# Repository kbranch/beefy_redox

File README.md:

# Beefy Redox
This uses the Redox layout with significant modifications to make it feel and sound sturdy.  It's dumb and overkill, but I like it.  PCB has been redone to work with Kailh MX hotswap sockets because Mill-Max sockets don't really fit some switches (like Kailh's box series).

Based on Mattia Dal Ben's Redox keyboard: https://github.com/mattdibi/redox-keyboard

Case based on Fosk_LL's design: https://www.thingiverse.com/thing:3607303

Associated hacked together firmware: https://github.com/kbranch/qmk_beefy_redox

Disasterous CAD files are available here:
https://cad.onshape.com/documents/79753b5942c6535c2d806763/w/4c8392e04a1d78f77636699a/e/d620deb7dfbc2bdc09fda4c7
https://cad.onshape.com/documents/7a9b7e869b26a13f2521e861/w/94ad519ba1de32380f27d44b/e/4a5e31582eda700c8368bdb9

## Printing

The STLs folder here on GitHub should include everything you need.  Some portions of the case are symmetrical, while others are not.  If there is no "Right" version of a model that has a "Left" version, use your slicer to mirror the left version to create the right version.

I used PrusaSlicer with my non-MMU printer to print the little LED diffuser bits in white by setting it up to let me manually change the filament at the right time, but you can also print the diffusers separately and install them after the fact.  The STLs folder has the separate plug as well as individual models suitable for importing as part of a multi-material file.

## Assembly

This is designed to use a separate plate for the switches - the "Redox_Plate.dxf" file should be suitable for sending to a company to be laser cut, although you will likely need to drill the M2 holes out to size.  I found stainless steel to sound best, but any other 1.5 mm thick material should also work.  The plate can be attached to the case with six M2 screws. I found that the sound improved when I offset the plate from the case with a little o-ring around each screw, but that's optional.

The case halves are designed to be held together with M3 screws.  There are pockets for M3 nuts - you may need to glue the nuts in place, the pockets are tricky to print well.

Note that the footprint for the microcontroller is wider than a Pro Micro due to PCB space limitations after turning the switch footprint into swiss cheese.  I floated a header off to the side of my Pro Micros with a bunch of fine wire to make it fit.

This uses four panel mount USB-C connectors - one for each controller, and one on each side for the connection between the two halves.  I used these, but there may be other places to get some with the same dimensions: https://www.adafruit.com/product/4053

The LED PCB uses these LEDs, 9 per side: https://www.adafruit.com/product/3484

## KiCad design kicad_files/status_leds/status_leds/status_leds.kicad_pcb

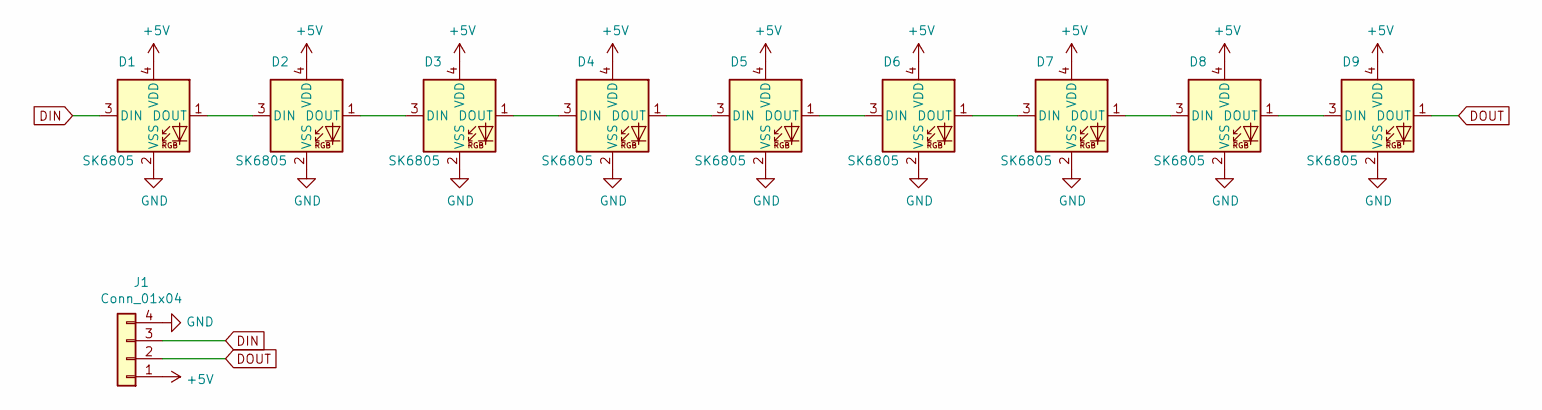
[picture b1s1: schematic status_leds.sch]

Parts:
D1, D2, D3, D4, D5, D6, D7, D8, D9: SK6805; LED_SK6805_PLCC4_2.4x2.7mm_P1.3mm
J1: Conn_01x04; JST_XH_B4B-XH-A_1x04_P2.50mm_Vertical

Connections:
+5V: D1.4 (VDD), D2.4 (VDD), D3.4 (VDD), D4.4 (VDD), D5.4 (VDD), D6.4 (VDD), D7.4 (VDD), D8.4 (VDD), D9.4 (VDD), J1.1
DIN: D1.3 (DIN), J1.3
DOUT: D9.1 (DOUT), J1.2
GND: D1.2 (VSS), D2.2 (VSS), D3.2 (VSS), D4.2 (VSS), D5.2 (VSS), D6.2 (VSS), D7.2 (VSS), D8.2 (VSS), D9.2 (VSS), J1.4
unnamed: D1.1 (DOUT), D2.3 (DIN)
unnamed: D2.1 (DOUT), D3.3 (DIN)
unnamed: D3.1 (DOUT), D4.3 (DIN)
unnamed: D4.1 (DOUT), D5.3 (DIN)
unnamed: D5.1 (DOUT), D6.3 (DIN)
unnamed: D6.1 (DOUT), D7.3 (DIN)
unnamed: D7.1 (DOUT), D8.3 (DIN)
unnamed: D8.1 (DOUT), D9.3 (DIN)

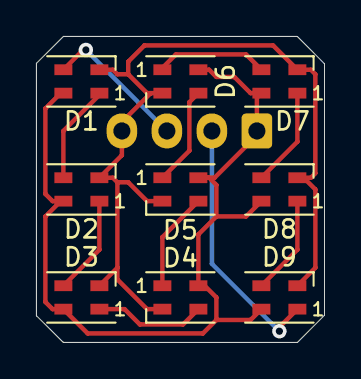
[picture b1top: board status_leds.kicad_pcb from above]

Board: 2 copper layers, 16.0 x 17.0 mm, 10 parts (1 on the bottom side), 12 nets.

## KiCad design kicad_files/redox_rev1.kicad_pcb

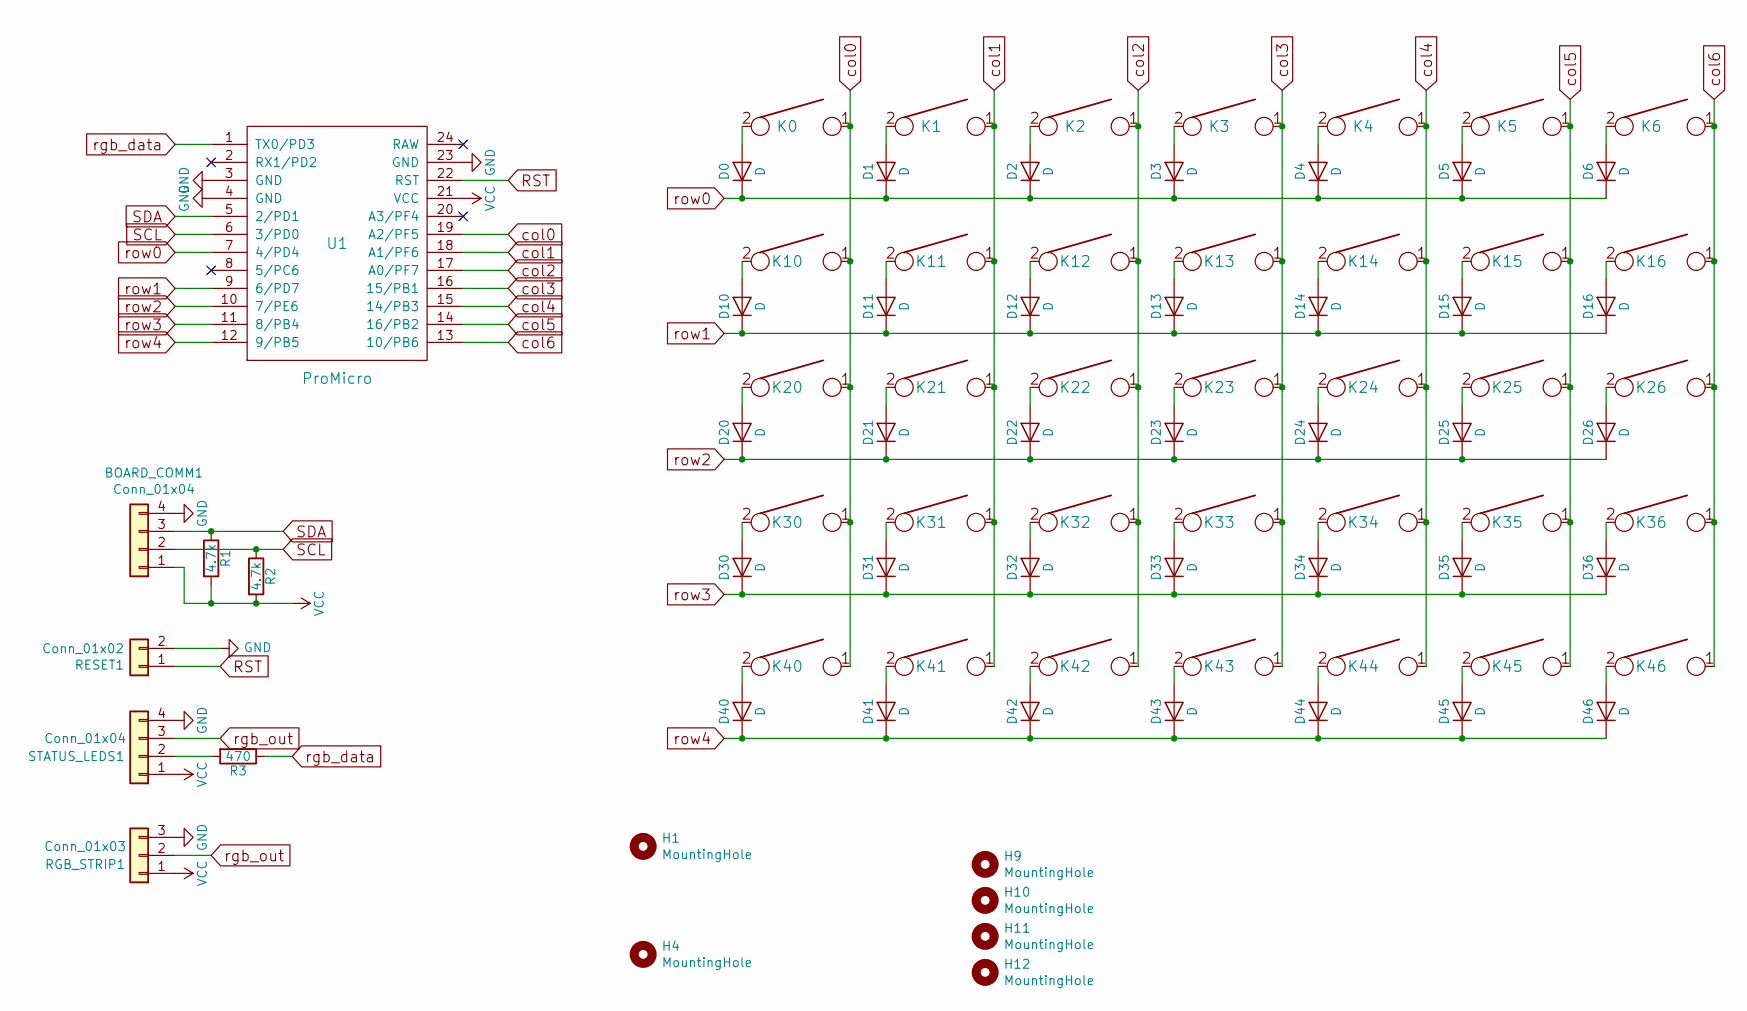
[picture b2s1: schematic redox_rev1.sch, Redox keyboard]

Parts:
BOARD_COMM1: Conn_01x04; JST_XH_S4B-XH-A_1x04_P2.50mm_Horizontal
D0, D1, D2, D3, D4, D5, D6, D10, D11, D12, D13, D14, D15, D16, D20, D21, D22, D23, D24, D25, D26, D30, D31, D32, D33, D34, D35, D36, D40, D41, D42, D43, D44, D45, D46: D; Diode-dual
H1, H4, H9, H10, H11, H12: MountingHole; MountingHole_2.2mm_M2
K0, K1, K2, K3, K4, K5, K6, K10, K11, K12, K13, K14, K15, K16, K20, K21, K22, K23, K24, K25, K26, K30, K31, K32, K33, K34, K35, K36, K40, K41, K42, K43, K44, K45, K46: KEYSW; Kailh_socket_MX_optional_reversible
R1, R2: 4.7k; Resistor-Compact
R3: 470; Resistor-Compact
RESET1: Conn_01x02; JST_XH_S2B-XH-A_1x02_P2.50mm_Horizontal
RGB_STRIP1: Conn_01x03; JST_XH_S3B-XH-A_1x03_P2.50mm_Horizontal
STATUS_LEDS1: Conn_01x04; JST_XH_S4B-XH-A_1x04_P2.50mm_Horizontal
U1: ProMicro; ArduinoProMicro-Wide

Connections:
GND: BOARD_COMM1.4, RESET1.2, RGB_STRIP1.3, STATUS_LEDS1.4, U1.3 (GND), U1.4 (GND), U1.23 (GND)
unnamed: D0.2 (A), K0.2
unnamed: D1.2 (A), K1.2
unnamed: D2.2 (A), K2.2
unnamed: D3.2 (A), K3.2
unnamed: D4.2 (A), K4.2
unnamed: D5.2 (A), K5.2
unnamed: D6.2 (A), K6.2
unnamed: D10.2 (A), K10.2
unnamed: D11.2 (A), K11.2
unnamed: D12.2 (A), K12.2
unnamed: D13.2 (A), K13.2
unnamed: D14.2 (A), K14.2
unnamed: D15.2 (A), K15.2
unnamed: D16.2 (A), K16.2
unnamed: D20.2 (A), K20.2
unnamed: D21.2 (A), K21.2
unnamed: D22.2 (A), K22.2
unnamed: D23.2 (A), K23.2
unnamed: D24.2 (A), K24.2
unnamed: D25.2 (A), K25.2
unnamed: D26.2 (A), K26.2
unnamed: D30.2 (A), K30.2
unnamed: D31.2 (A), K31.2
unnamed: D32.2 (A), K32.2
unnamed: D33.2 (A), K33.2
unnamed: D34.2 (A), K34.2
unnamed: D35.2 (A), K35.2
unnamed: D36.2 (A), K36.2
unnamed: D40.2 (A), K40.2
unnamed: D41.2 (A), K41.2
unnamed: D42.2 (A), K42.2
unnamed: D43.2 (A), K43.2
unnamed: D44.2 (A), K44.2
unnamed: D45.2 (A), K45.2
unnamed: D46.2 (A), K46.2
unnamed: R3.2, STATUS_LEDS1.2
RST: RESET1.1, U1.22 (RST)
SCL: BOARD_COMM1.2, R2.1, U1.6 (3/PD0)
SDA: BOARD_COMM1.3, R1.1, U1.5 (2/PD1)
VCC: BOARD_COMM1.1, R1.2, R2.2, RGB_STRIP1.1, STATUS_LEDS1.1, U1.21 (VCC)
col0: K0.1, K10.1, K20.1, K30.1, K40.1, U1.19 (A2/PF5)
col1: K1.1, K11.1, K21.1, K31.1, K41.1, U1.18 (A1/PF6)
col2: K2.1, K12.1, K22.1, K32.1, K42.1, U1.17 (A0/PF7)
col3: K3.1, K13.1, K23.1, K33.1, K43.1, U1.16 (15/PB1)
col4: K4.1, K14.1, K24.1, K34.1, K44.1, U1.15 (14/PB3)
col5: K5.1, K15.1, K25.1, K35.1, K45.1, U1.14 (16/PB2)
col6: K6.1, K16.1, K26.1, K36.1, K46.1, U1.13 (10/PB6)
rgb_data: R3.1, U1.1 (TX0/PD3)
rgb_out: RGB_STRIP1.2, STATUS_LEDS1.3
row0: D0.1 (K), D1.1 (K), D2.1 (K), D3.1 (K), D4.1 (K), D5.1 (K), D6.1 (K), U1.7 (4/PD4)
row1: D10.1 (K), D11.1 (K), D12.1 (K), D13.1 (K), D14.1 (K), D15.1 (K), D16.1 (K), U1.9 (6/PD7)
row2: D20.1 (K), D21.1 (K), D22.1 (K), D23.1 (K), D24.1 (K), D25.1 (K), D26.1 (K), U1.10 (7/PE6)
row3: D30.1 (K), D31.1 (K), D32.1 (K), D33.1 (K), D34.1 (K), D35.1 (K), D36.1 (K), U1.11 (8/PB4)
row4: D40.1 (K), D41.1 (K), D42.1 (K), D43.1 (K), D44.1 (K), D45.1 (K), D46.1 (K), U1.12 (9/PB5)

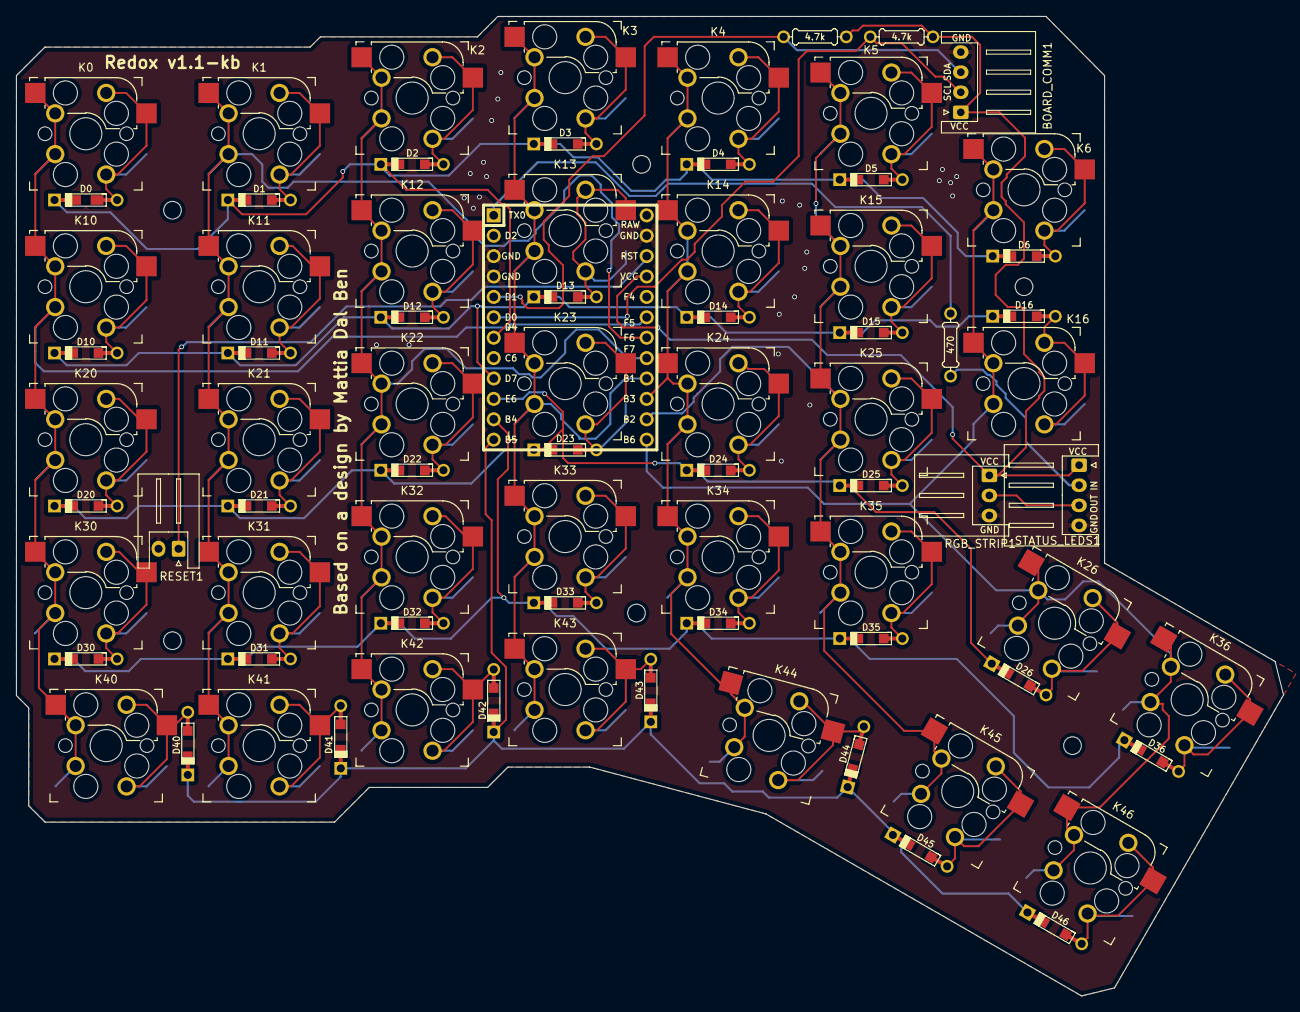
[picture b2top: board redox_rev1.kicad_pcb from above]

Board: 2 copper layers, 157.8 x 122.0 mm, 84 parts (0 on the bottom side), 55 nets.

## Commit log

2020-09-06 Added STLs
